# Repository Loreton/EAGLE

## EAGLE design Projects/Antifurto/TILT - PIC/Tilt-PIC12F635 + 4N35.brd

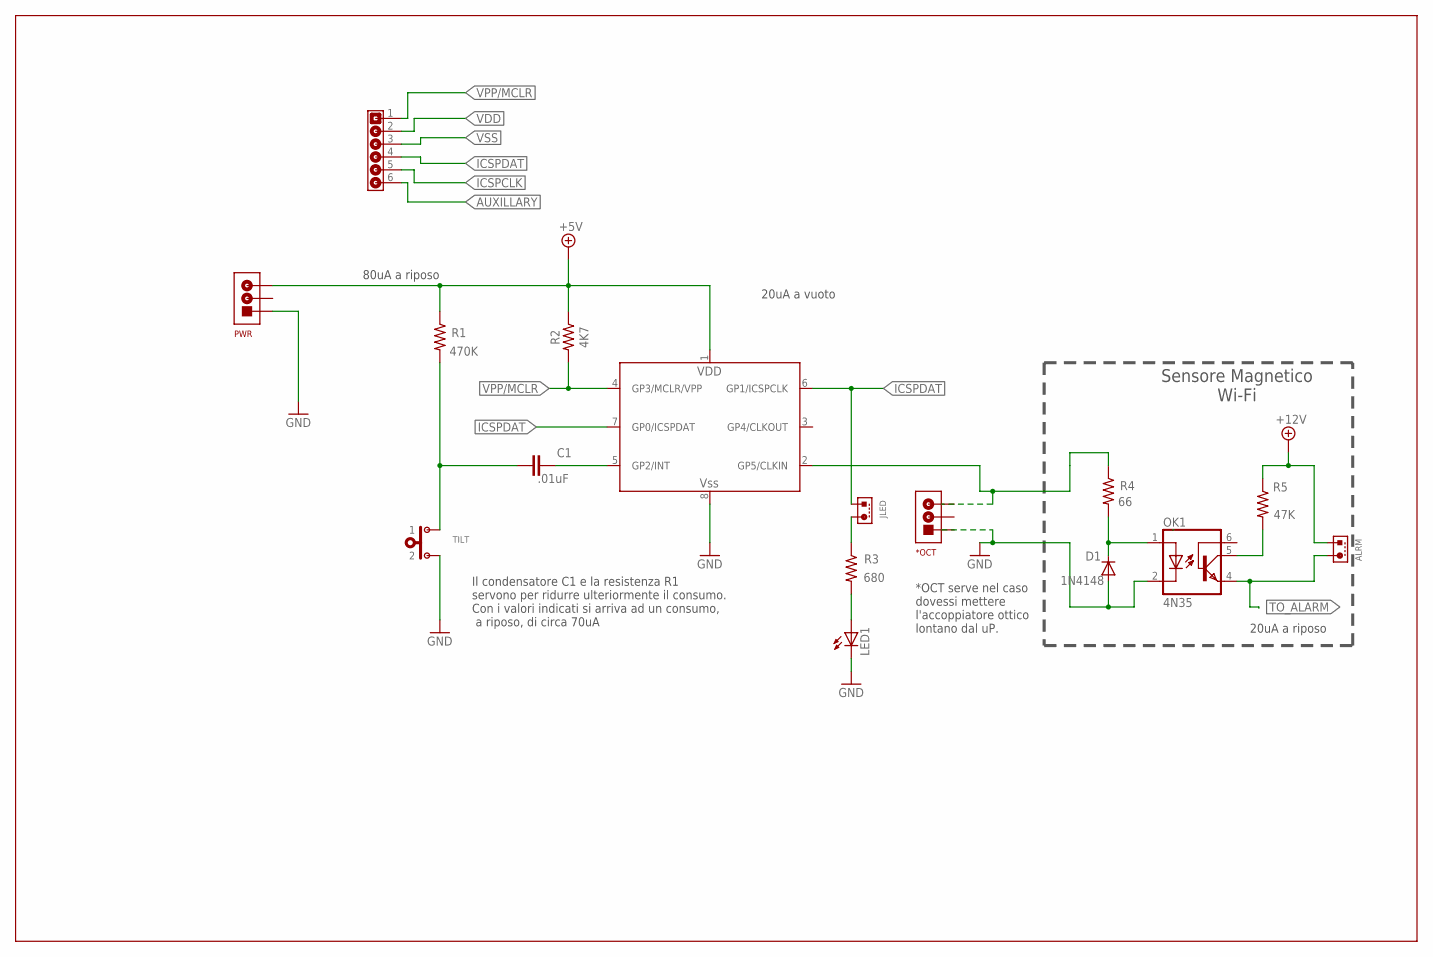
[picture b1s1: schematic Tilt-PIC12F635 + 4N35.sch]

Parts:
*OCT: MAMMUTH03
ALRM: JUMPER2X1; SIP02
C1: .01uF; C025-024X044
D1: 1N4148; DO35-10
JLED: JUMPER2X1; SIP02
LED1: LED5MM
OK1: 4N35; DIL06
PWR: MAMMUTH03
R1: 470K; 0207/12
R2: 4K7; 0207/12
R3: 680; 0207/12
R4: 66; 0207/12
R5: 47K; 0207/12
TILT: PULSANTENO; SIP02
U$1: SIP06
UP1: PIC12F635; DIL8

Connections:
+5V: PWR.P$3 (3), R1.1, R2.1, UP1.1 (VDD)
+12V: ALRM.1, R5.1
AUXILLARY: U$1.6
GND: D1.A, OK1.2 (C), PWR.P$1 (1), TILT.2
ICSPCLK: U$1.5
ICSPDAT: JLED.1, U$1.4, UP1.6 (GP1/ICSPCLK)
unnamed: LED1.A, R3.2
unnamed: R4.1, UP1.2 (GP5/CLKIN)
unnamed: C1.2, UP1.5 (GP2/INT)
unnamed: JLED.2, R3.1
unnamed: D1.C, OK1.1 (A), R4.2
unnamed: OK1.5 (COL), R5.2
TILT: C1.1, R1.2, TILT.1
TO_ALARM: ALRM.2, OK1.4 (EMI)
VDD: U$1.2
VPP/MCLR: R2.2, U$1.1, UP1.4 (GP3/MCLR/VPP)
VSS: LED1.K (C), U$1.3, UP1.8 (VSS)

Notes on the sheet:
Sensore Magnetico Wi-Fi
Il condensatore C1 e la resistenza R1 servono per ridurre ulteriormente il consumo. Con i valori indicati si arriva ad un consumo, a riposo, di circa 70uA
20uA a riposo
20uA a vuoto
80uA a riposo
*OCT serve nel caso dovessi mettere l'accoppiatore ottico lontano dal uP.

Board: 2 copper layers, 16 parts (0 on the bottom side), 14 nets, no tracks yet.

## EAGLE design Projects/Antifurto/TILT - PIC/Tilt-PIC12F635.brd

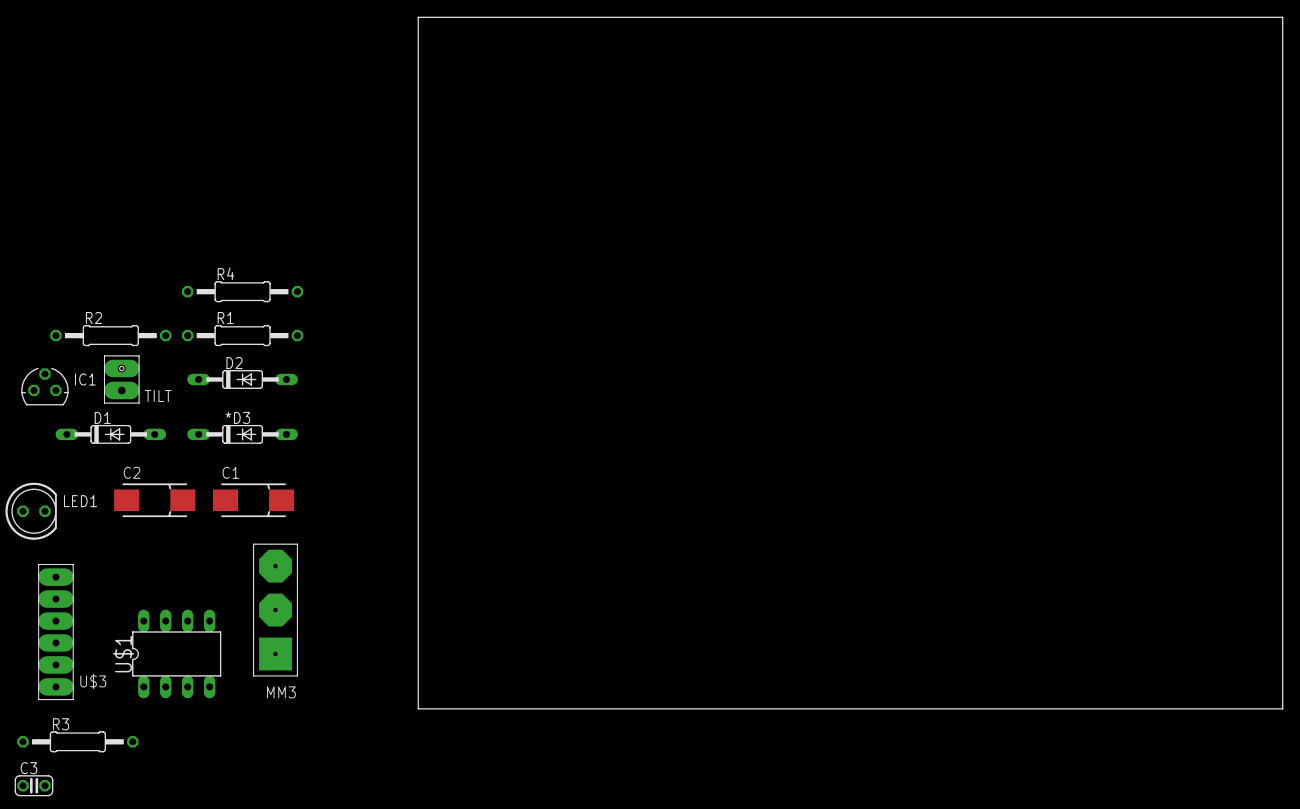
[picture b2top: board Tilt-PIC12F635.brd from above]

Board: 2 copper layers, 100.0 x 80.0 mm, 16 parts (0 on the bottom side), 8 nets, no tracks yet.

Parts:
*D3: 1N4148; DO35-10
C1, C2: 100uF; 085CS_1AR
C3: C025-024X044
D1, D2: 1N4148; DO35-10
IC1: 78LXX
LED1: LED5MM
MM3: MAMMUTH03
R1, R2, R3, R4: 4K7; 0207/12
TILT: PULSANTENO; SIP02
U$1: PIC12F635; DIL8
U$3: SIP06

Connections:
+12V: C1.+, IC1.IN, MM3.P$3
unnamed: LED1.A, R1.2
unnamed: R1.1, U$1.2
unnamed: *D3.A, C2.+, R2.2
unnamed: D1.C, D2.C, R4.2
VDD: IC1.OUT, R2.1, U$1.1, U$3.2
VPP/MCLR: *D3.C, U$1.4, U$3.1
VSS: C1.-, IC1.GND, LED1.K, MM3.P$1, TILT.2, U$1.8, U$3.3

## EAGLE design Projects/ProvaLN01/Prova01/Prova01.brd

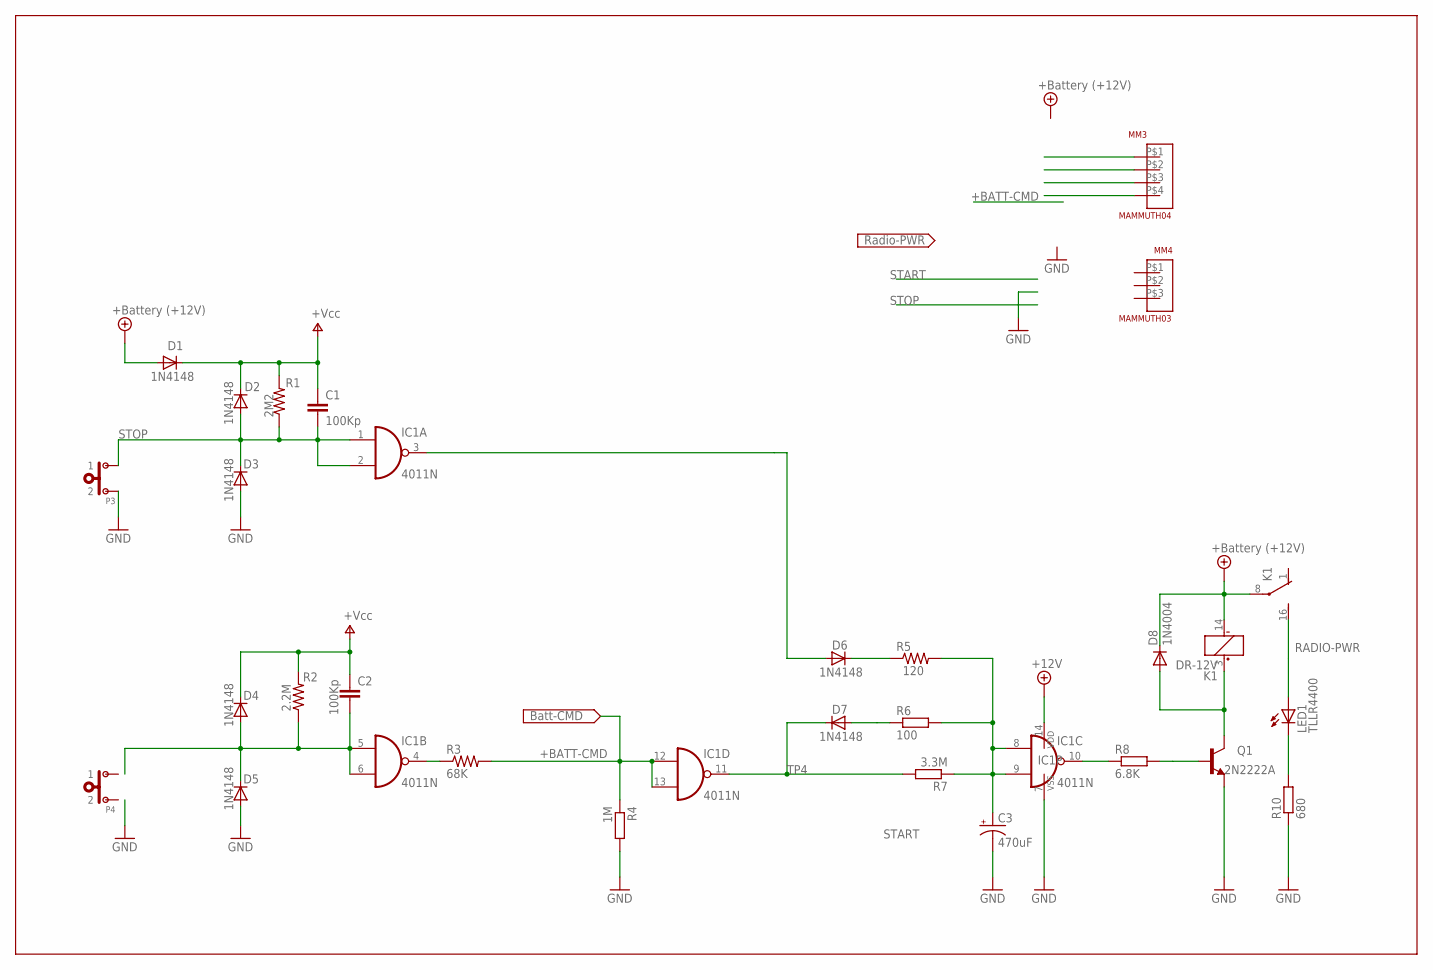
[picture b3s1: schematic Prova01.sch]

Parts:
C1, C2: 100Kp; C025-025X050
C3: 470uF; E3,5-8
D1, D2, D3, D4, D5, D6, D7: 1N4148; DO35-10
D8: 1N4004; DO41-10
IC1: 4011N; DIL14
K1: DR-12V; DR-1
LED1: TLLR4400; LED3MM
MM3: MAMMUTH04
MM4: MAMMUTH03
P3, P4: PULSANTENO; SIP02
Q1: 2N2222A; TO18
R1: 2M2; 0207/12
R2: 2.2M; 0207/12
R3: 68K; 0207/12
R4: 1M; 0207/10
R5: 120; 0207/12
R6: 100; 0207/10
R7: 3.3M; 0207/10
R8: 6.8K; 0207/10
R10: 680; 0207/10

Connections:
+12V: D1.A, D8.C, IC1.14 (VDD), K1.8, K1.14 (-)
+BATT-CMD: IC1.12 (I0), IC1.13 (I1), R3.2, R4.1
GND: C3.-, D3.A, D5.A, IC1.7 (VSS), P3.2, Q1.1 (E), R4.2, R10.1
unnamed: C2.2, D4.A, D5.C, IC1.5 (I0), IC1.6 (I1), R2.1
unnamed: Q1.2 (B), R8.2
unnamed: D8.A, K1.3 (+), Q1.3 (C)
unnamed: D6.C, R5.1
unnamed: IC1.4 (O), R3.1
unnamed: LED1.K (C), R10.2
unnamed: D6.A, IC1.3 (O)
RADIO-PWR: K1.16 (S), LED1.A
START: D7.A, R6.1
STOP: C1.2, D2.A, D3.C, IC1.1 (I0), IC1.2 (I1), P3.1, R1.1
TP4: D7.C, IC1.11 (O), R7.2
TP4A: C3.+, IC1.8 (I0), IC1.9 (I1), R5.2, R6.2, R7.1
TP5: IC1.10 (O), R8.1
V+: C1.1, C2.1, D1.C, D2.C, D4.C, R1.2, R2.2

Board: 2 copper layers, 28 parts (0 on the bottom side), 17 nets, no tracks yet.

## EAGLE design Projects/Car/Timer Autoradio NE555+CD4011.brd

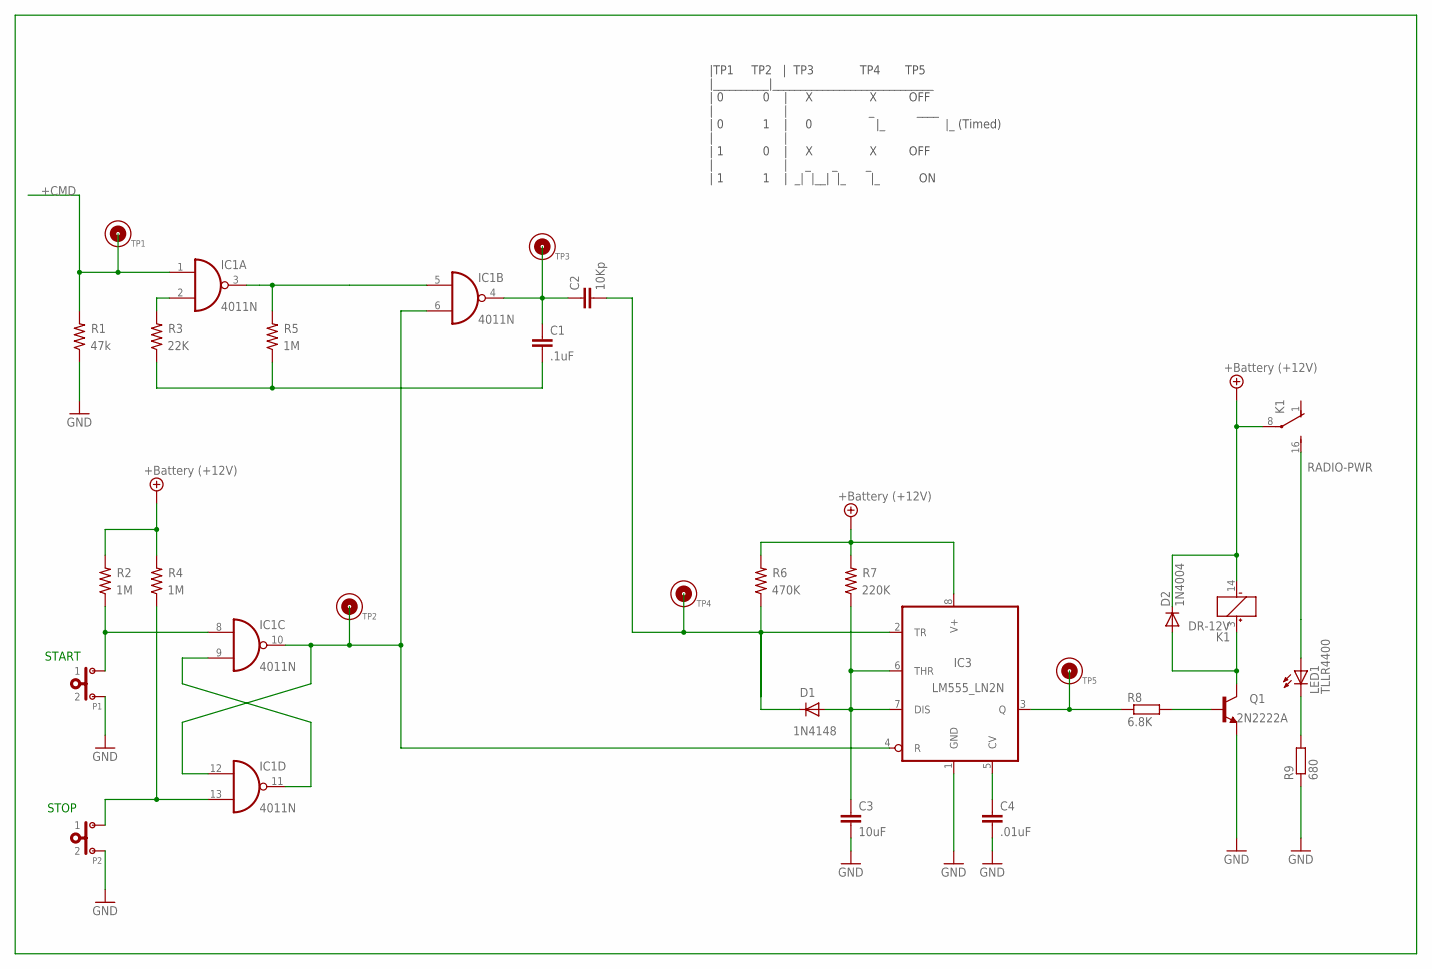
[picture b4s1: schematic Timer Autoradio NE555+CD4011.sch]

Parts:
C1: .1uF; C025-040X050
C2: 10Kp; C025-040X050
C3: 10uF; C025-040X050
C4: .01uF; C025-040X050
D1: 1N4148; DO35-10
D2: 1N4004; DO41-10
IC1: 4011N; DIL14
IC3: LM555_LN2N; DIL08
K1: DR-12V; DR-1
LED1: TLLR4400; LED3MM
P1, P2: PULSANTENO; SIP02
Q1: 2N2222A; TO18
R1: 47k; 0207/12
R2, R4, R5: 1M; 0207/12
R3: 22K; 0207/12
R6: 470K; 0207/12
R7: 220K; 0207/12
R8: 6.8K; 0207/10
R9: 680; 0207/10
TP1, TP2, TP3, TP4, TP5: SIP01

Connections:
+12V: D2.C, IC3.8 (V+), K1.8, K1.14 (-), R2.2, R4.2, R6.2, R7.2
+CMD: IC1.1 (I0), R1.2, TP1.P$1
GND: C3.2, C4.2, IC3.1 (GND), P1.2, P2.2, Q1.1 (E), R1.1, R9.1
unnamed: C1.2, R3.1, R5.1
unnamed: Q1.2 (B), R8.2
unnamed: D2.A, K1.3 (+), Q1.3 (C)
unnamed: C4.1, IC3.5 (CV)
unnamed: IC1.3 (O), IC1.5 (I0), R5.2
unnamed: C1.1, C2.1, IC1.4 (O), TP3.P$1
unnamed: IC1.2 (I1), R3.2
unnamed: LED1.K (C), R9.2
unnamed: IC1.8 (I0), P1.1, R2.1
unnamed: IC3.3 (Q), R8.1, TP5.P$1
unnamed: IC1.6 (I1), IC1.10 (O), IC1.12 (I0), IC3.4 (R), TP2.P$1
unnamed: IC1.9 (I1), IC1.11 (O)
unnamed: C2.2, D1.C, IC3.2 (TR), R6.1, TP4.P$1
unnamed: IC1.13 (I1), P2.1, R4.1
unnamed: C3.1, D1.A, IC3.6 (THR), IC3.7 (DIS), R7.1
RADIO-PWR: K1.16 (S), LED1.A
VDD: IC1.14 (VDD)
VSS: IC1.7 (VSS)

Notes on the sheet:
START
STOP
|TP1 TP2 | TP3 TP4 TP5 |__________|_____________________________ | 0 0 | X X OFF | | _ ____ | 0 1 | 0 |_ |_ (Timed) | | | 1 0 | X X OFF | | _ _ _ | 1 1 | _| |__| |_ |_ ON

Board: 2 copper layers, 27 parts (0 on the bottom side), 19 nets, no tracks yet.

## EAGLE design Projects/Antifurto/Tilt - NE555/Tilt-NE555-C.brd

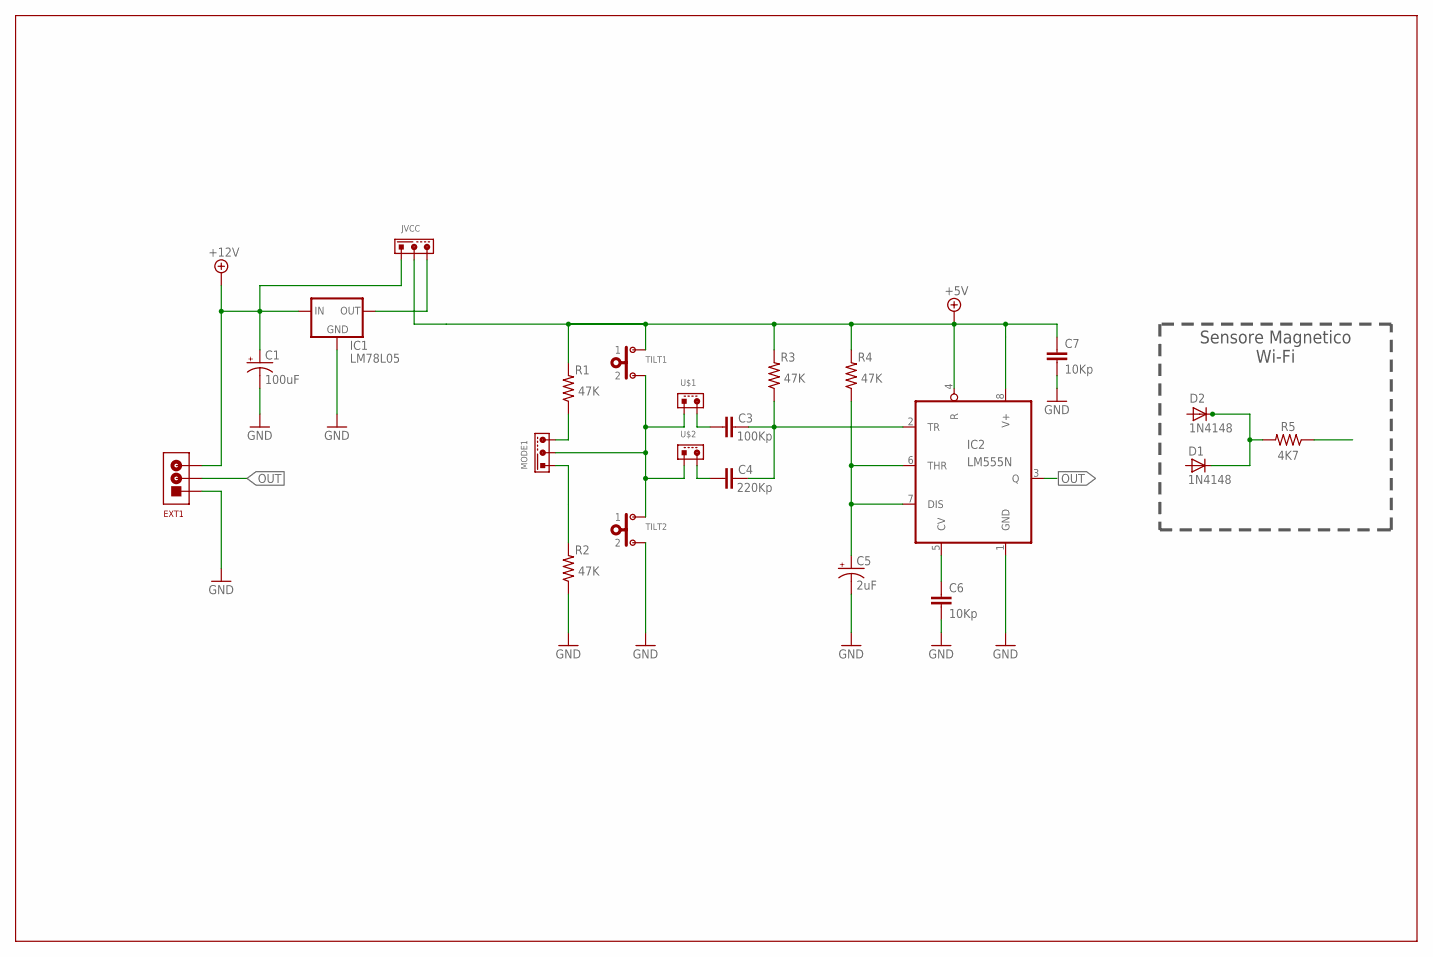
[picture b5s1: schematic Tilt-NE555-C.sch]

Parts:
C1: 100uF; E5-5
C3: 100Kp; C075-032X103
C4: 220Kp; C050-035X075
C5: 2uF; E5-5
C6, C7: 10Kp; C050-035X075
D1, D2: 1N4148; DO35-10
EXT1: MAMMUTH03
IC1: LM78L05; 78LXX
IC2: LM555N; DIL08
JVCC: JUMPER3; SIP03
MODE1: JUMPER3; SIP03
R1, R2, R3, R4: 47K; 0207/15
R5: 4K7; 0207/12
TILT1, TILT2: PULSANTENO; SIP02
U$1, U$2: JUMPER2X1; SIP02

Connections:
+5V: C7.1, IC2.4 (R), IC2.8 (V+), JVCC.1 (2), R1.2, R3.2, R4.2, TILT1.1
+12V: C1.+, EXT1.P$3 (3), IC1.IN, JVCC.2 (1)
GND: C1.-, C5.-, C6.2, C7.2, EXT1.P$1 (1), IC1.GND, IC2.1 (GND), R2.1, TILT2.2
unnamed: C3.2, C4.2, IC2.2 (TR), R3.1
unnamed: MODE1.1 (2), TILT1.2, TILT2.1, U$1.1, U$2.1
unnamed: C5.+, IC2.6 (THR), IC2.7 (DIS), R4.1
unnamed: C6.1, IC2.5 (CV)
unnamed: MODE1.2 (1), R2.2
unnamed: D1.C, D2.C, R5.2
unnamed: IC1.OUT, JVCC.3
unnamed: C4.1, U$2.2
unnamed: C3.1, U$1.2
unnamed: MODE1.3, R1.1
OUT: EXT1.P$2 (2), IC2.3 (Q)
SENSORE: R5.1

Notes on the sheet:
Sensore Magnetico Wi-Fi

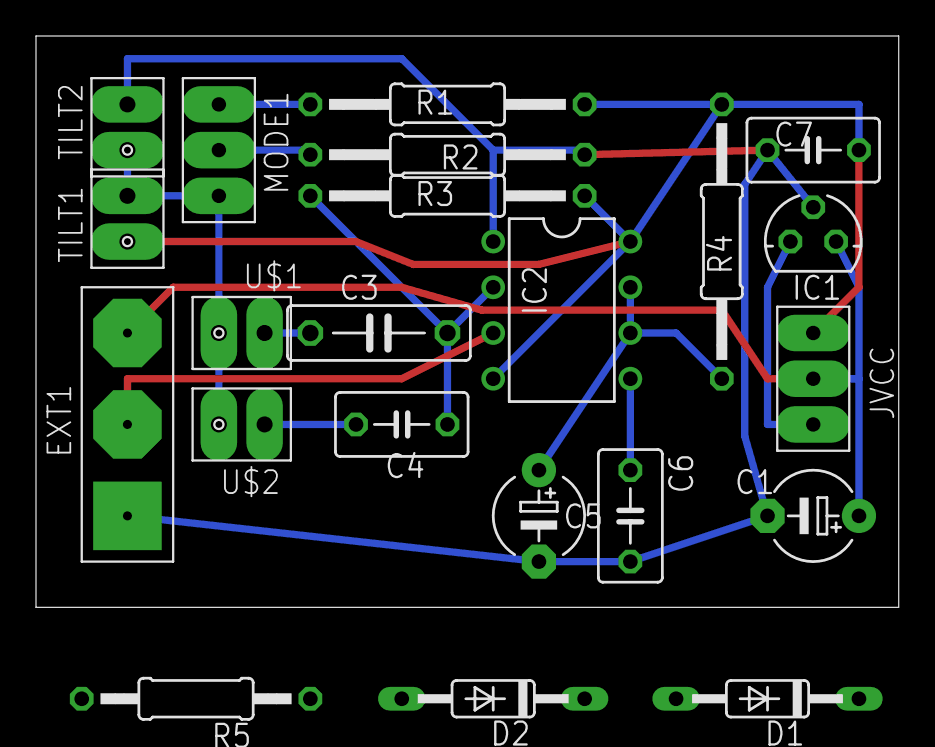
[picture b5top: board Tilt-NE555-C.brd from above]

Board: 2 copper layers, 47.9 x 31.7 mm, 22 parts (0 on the bottom side), 14 nets.

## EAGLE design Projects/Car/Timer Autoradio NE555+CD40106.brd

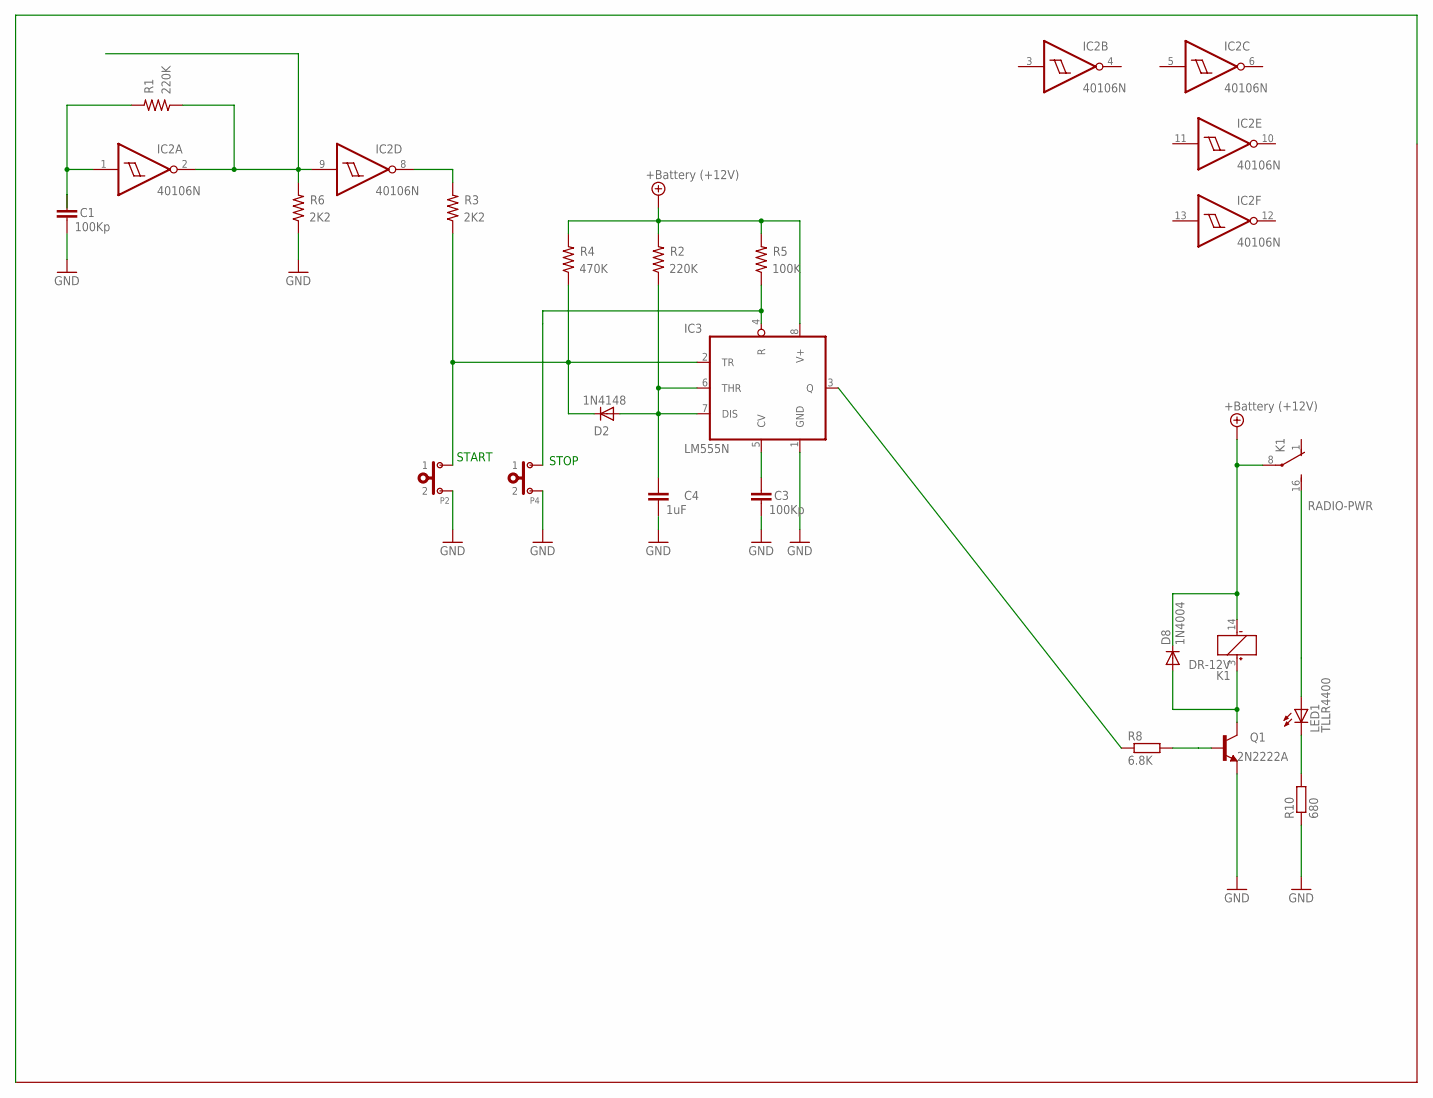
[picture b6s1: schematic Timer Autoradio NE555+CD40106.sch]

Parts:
C1, C3: 100Kp; C025-025X050
C4: 1uF; C025-025X050
D2: 1N4148; DO35-10
D8: 1N4004; DO41-10
IC2: 40106N; DIL14
IC3: LM555N; DIL08
K1: DR-12V; DR-1
LED1: TLLR4400; LED3MM
P2, P4: PULSANTENO; SIP02
Q1: 2N2222A; TO18
R1, R2: 220K; 0207/12
R3, R6: 2K2; 0207/12
R4: 470K; 0207/12
R5: 100K; 0207/12
R8: 6.8K; 0207/10
R10: 680; 0207/10

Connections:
+12V: D8.C, IC3.8 (V+), K1.8, K1.14 (-), R2.2, R4.2, R5.2
GND: IC3.1 (GND), P2.2, P4.2, Q1.1 (E), R6.1, R10.1
unnamed: Q1.2 (B), R8.2
unnamed: D8.A, K1.3 (+), Q1.3 (C)
unnamed: C3.1, IC3.5 (CV)
unnamed: IC2.9 (I), R6.2
unnamed: C1.1, IC2.1 (I), R1.2
unnamed: LED1.K (C), R10.2
unnamed: IC3.3 (Q), R8.1
unnamed: IC3.4 (R), P4.1, R5.1
unnamed: D2.C, IC3.2 (TR), P2.1, R3.1, R4.1
unnamed: C4.1, D2.A, IC3.6 (THR), IC3.7 (DIS), R2.1
RADIO-PWR: K1.16 (S), LED1.A
VDD: IC2.14 (VDD)
VSS: IC2.7 (VSS)

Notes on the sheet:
START
STOP

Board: 2 copper layers, 20 parts (0 on the bottom side), 13 nets, no tracks yet.

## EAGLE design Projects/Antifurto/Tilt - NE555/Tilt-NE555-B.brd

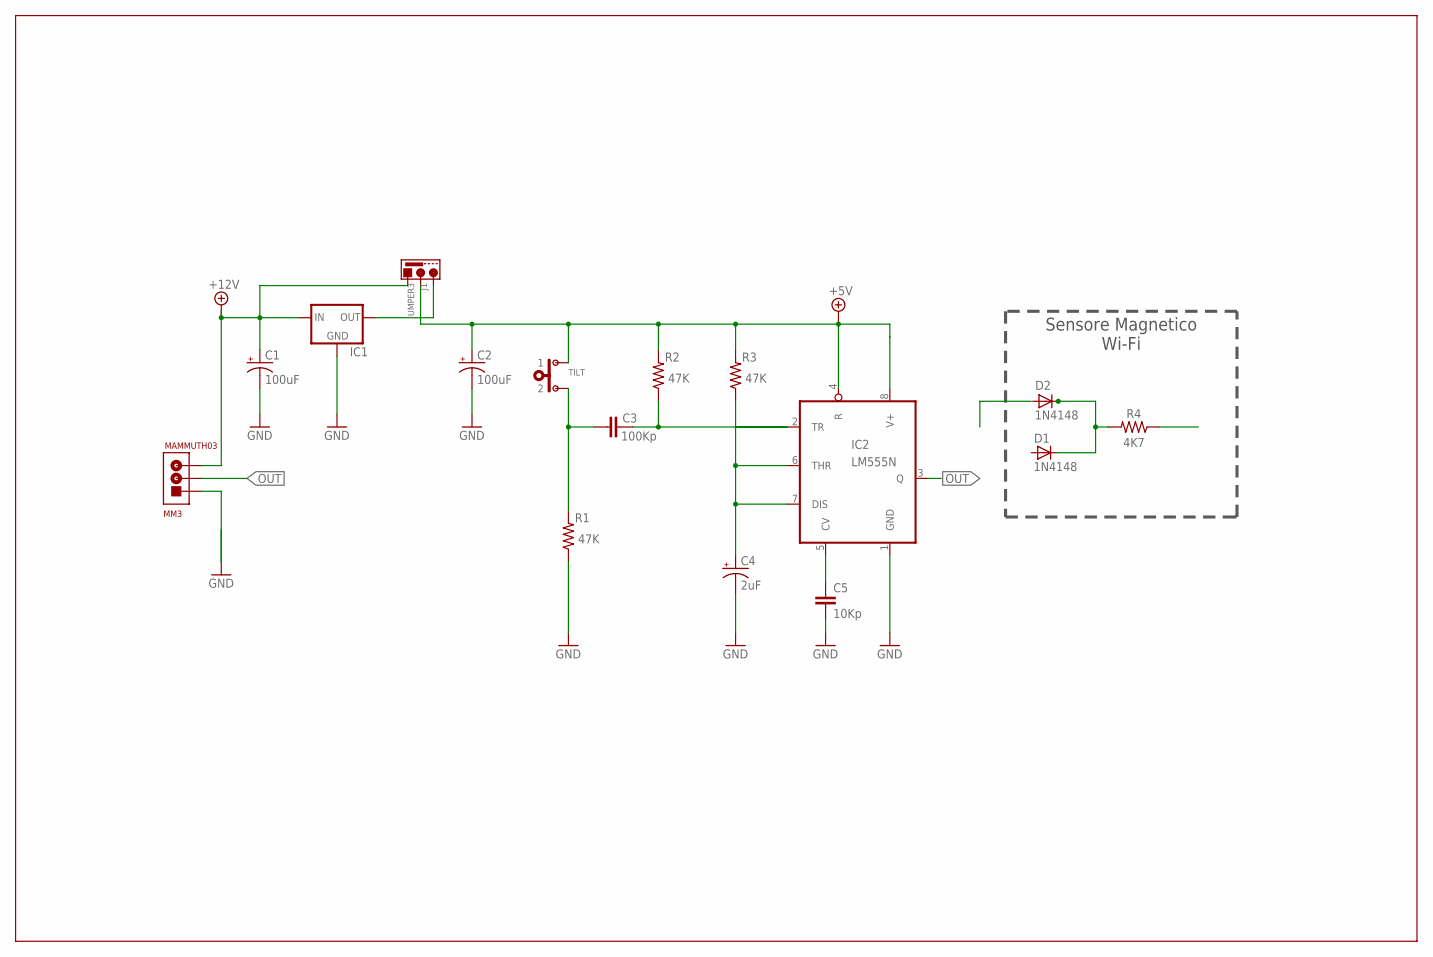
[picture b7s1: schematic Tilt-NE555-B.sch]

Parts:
C1, C2: 100uF; 085CS_1AR
C3: 100Kp; C025-025X050
C4: 2uF; 085CS_1AR
C5: 10Kp; C025-025X050
D1, D2: 1N4148; DO35-10
IC1: 78LXX
IC2: LM555N; DIL08
J1: JUMPER3; SIP03
MM3: MAMMUTH03
R1, R2, R3: 47K; 0207/12
R4: 4K7; 0207/12
TILT: PULSANTENO; SIP02

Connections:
+5V: C2.+, IC2.4 (R), IC2.8 (V+), J1.1, R2.2, R3.2, TILT.1
+12V: C1.+, IC1.IN, J1.2, MM3.P$3 (3)
GND: C1.-, C2.-, C4.-, C5.2, IC1.GND, IC2.1 (GND), MM3.P$1 (1), R1.1
unnamed: C3.2, IC2.2 (TR), R2.1
unnamed: C3.1, R1.2, TILT.2
unnamed: C4.+, IC2.6 (THR), IC2.7 (DIS), R3.1
unnamed: C5.1, IC2.5 (CV)
unnamed: D1.C, D2.C, R4.2
unnamed: IC1.OUT, J1.3
OUT: IC2.3 (Q), MM3.P$2 (2)
SENSORE: R4.1

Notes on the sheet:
Sensore Magnetico Wi-Fi

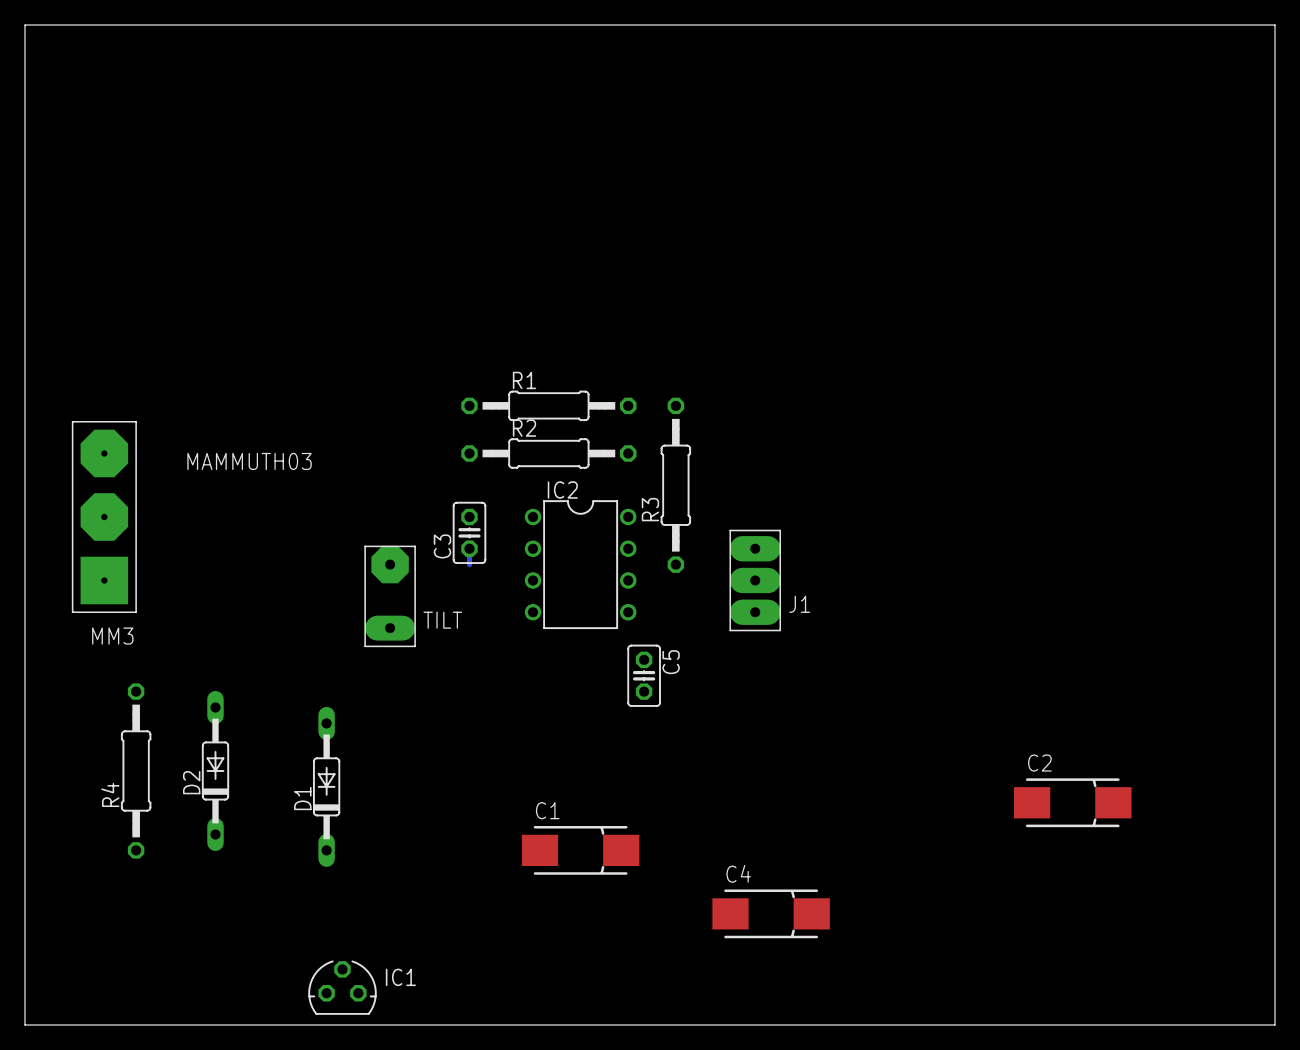
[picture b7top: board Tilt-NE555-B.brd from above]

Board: 2 copper layers, 100.0 x 80.0 mm, 16 parts (0 on the bottom side), 10 nets.

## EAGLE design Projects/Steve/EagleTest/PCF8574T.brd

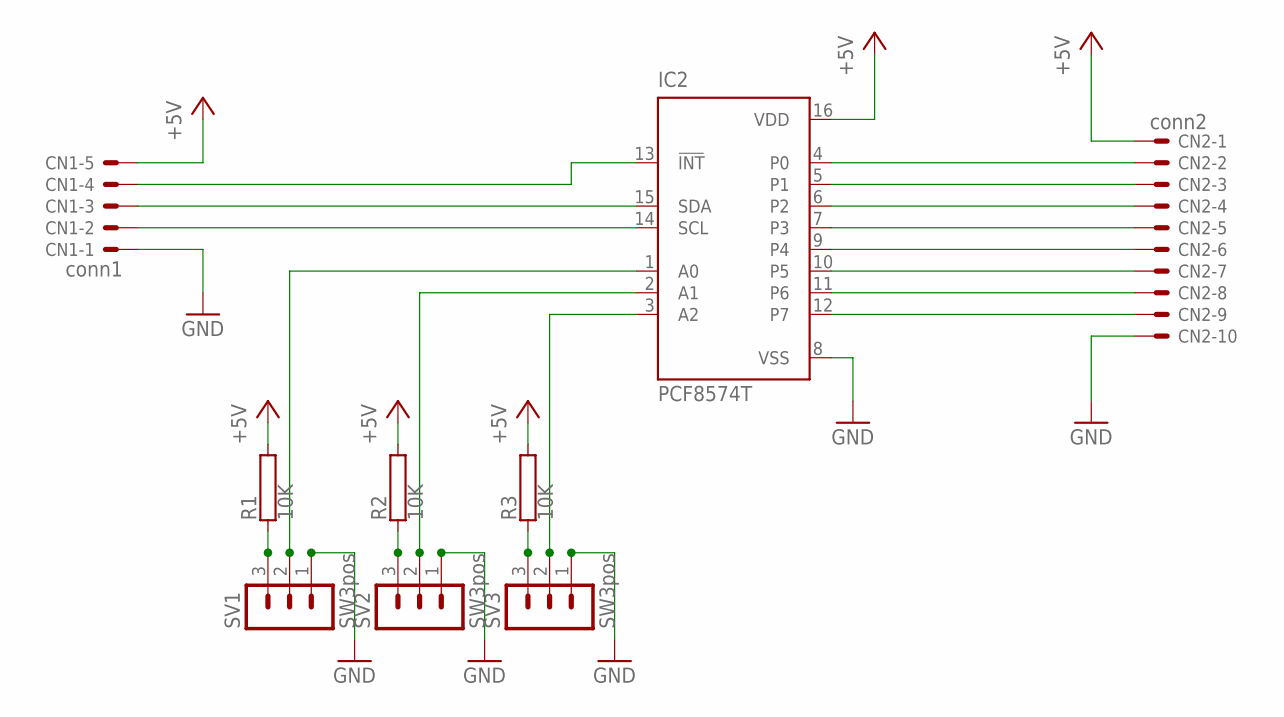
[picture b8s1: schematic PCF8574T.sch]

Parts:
CN1: conn1; 22-23-2051
CN2: conn2; 22-23-2101
IC2: PCF8574T; SO16W
R1, R2, R3: 10K; HPS58
SV1, SV2, SV3: SW3pos; MA03-1

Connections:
+5V: CN1.5, CN2.1, IC2.16 (VDD), R1.2, R2.2, R3.2
unnamed: R1.1, SV1.3
unnamed: R2.1, SV2.3
unnamed: R3.1, SV3.3
unnamed: IC2.1 (A0), SV1.2
unnamed: IC2.2 (A1), SV2.2
unnamed: IC2.3 (A2), SV3.2
unnamed: CN1.4, IC2.13 (!INT)
unnamed: CN1.1, CN2.10, IC2.8 (VSS), SV1.1, SV2.1, SV3.1
unnamed: CN2.2, IC2.4 (P0)
unnamed: CN2.3, IC2.5 (P1)
unnamed: CN2.4, IC2.6 (P2)
unnamed: CN2.5, IC2.7 (P3)
unnamed: CN2.6, IC2.9 (P4)
unnamed: CN2.7, IC2.10 (P5)
unnamed: CN2.8, IC2.11 (P6)
unnamed: CN2.9, IC2.12 (P7)
unnamed: CN1.2, IC2.14 (SCL)
unnamed: CN1.3, IC2.15 (SDA)

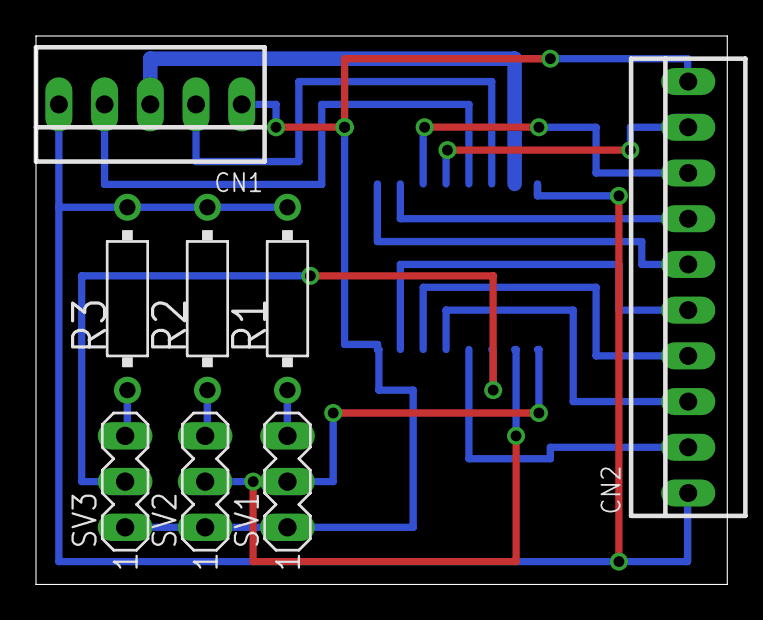
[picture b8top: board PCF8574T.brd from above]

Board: 2 copper layers, 38.4 x 30.5 mm, 9 parts (1 on the bottom side), 19 nets.

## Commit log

2014-03-02 starting project
2014-03-02 started TILT PIC project
2014-04-03 aggiornameti PIC12F635 + 4N35.sch
2015-02-06 2015-02-06 07:54 - commit with no comment
